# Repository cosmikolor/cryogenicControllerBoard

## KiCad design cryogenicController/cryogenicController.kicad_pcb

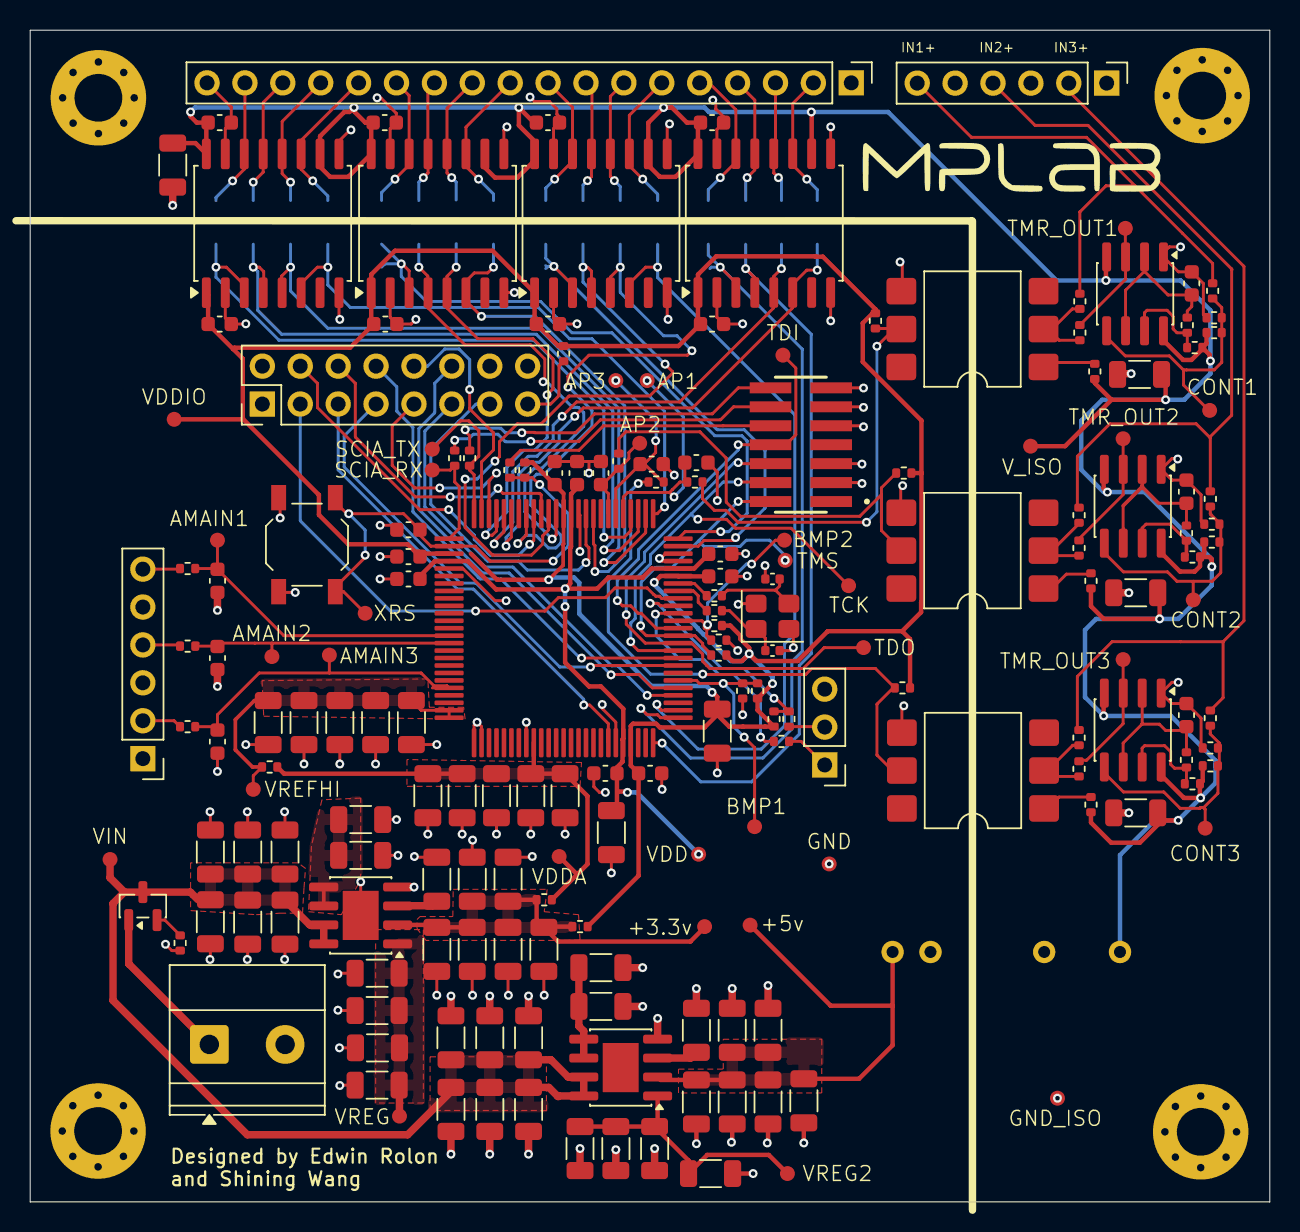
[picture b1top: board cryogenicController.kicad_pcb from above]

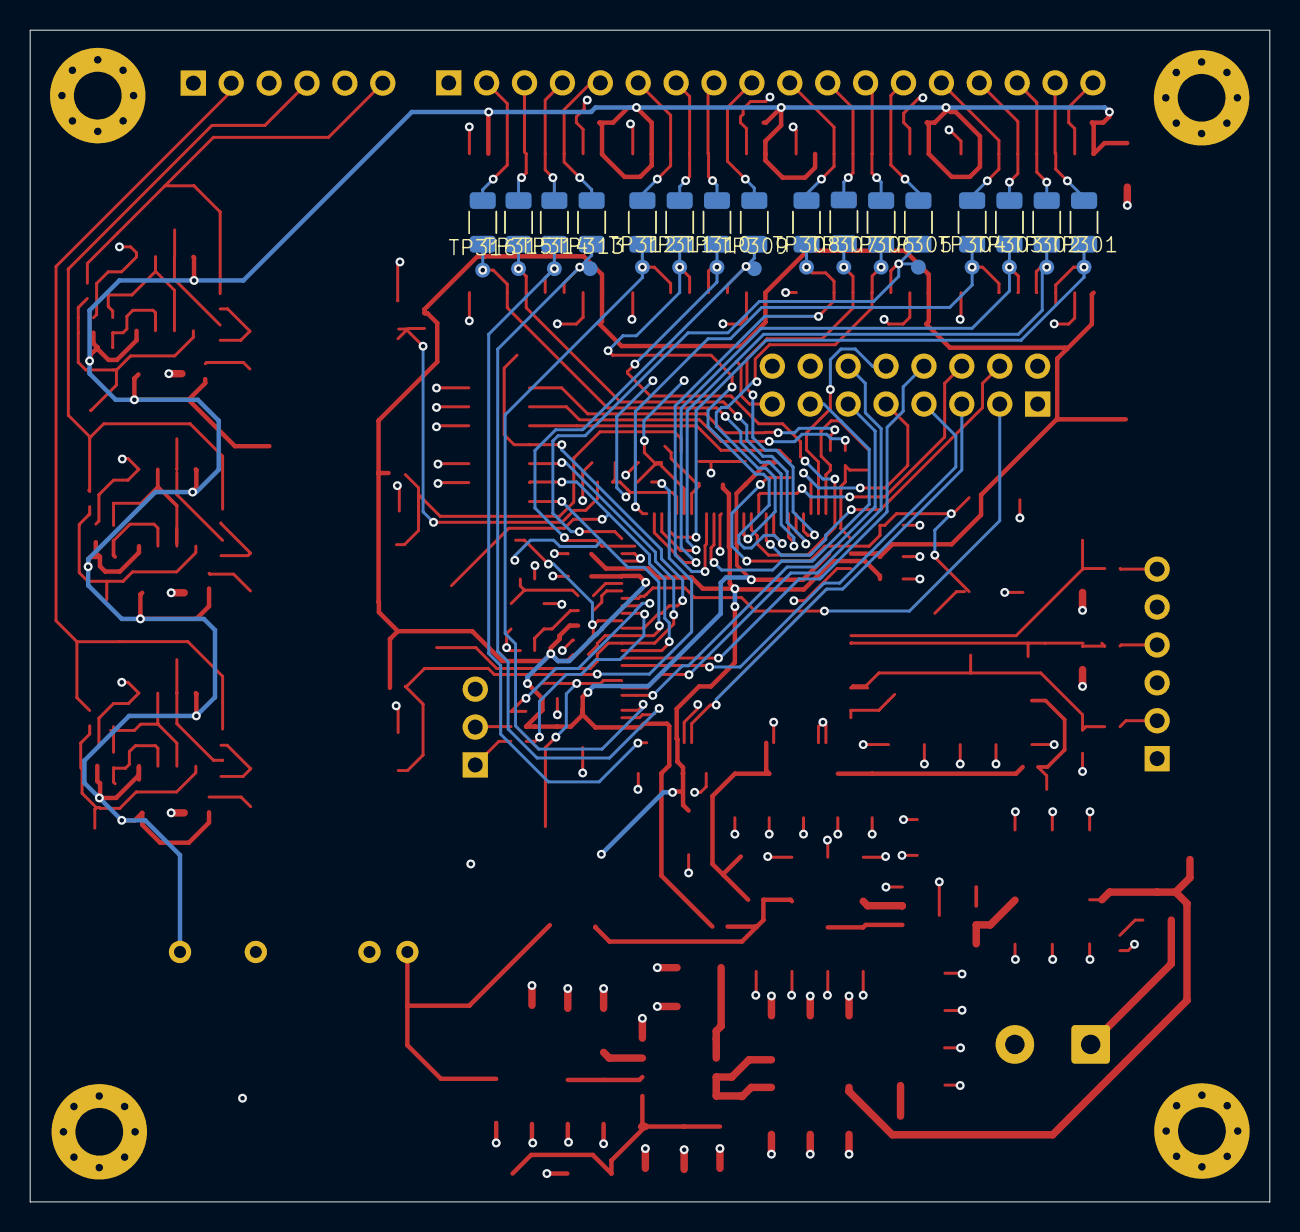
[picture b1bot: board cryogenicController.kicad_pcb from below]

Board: 4 copper layers, 83.1 x 78.5 mm, 223 parts (32 on the bottom side), 115 nets.

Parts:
+3.3v, +5v: TestPoint; Testpoint_1.0mm
AMAIN1, AMAIN2, AMAIN3: TestPoint; Testpoint_1.0mm
AP1, AP2, AP3: TestPoint; Testpoint_1.0mm
BMP1, BMP2: TestPoint; Testpoint_1.0mm
C201, C202, C203, C204, C205, C206, C207, C208, C209, C210, C211, C212, C213, C214, C215, C216, C217, C218, C219, C220, C221, C222, C223, C224, C225, C226, C227, C228, C229, C230, C231, C232, C233, C234, C235, C236, C237, C238, C301, C402, C405, C408, C503, C504, C505, C506, C507, C510, C511, C514, C515, C519, C522, C523: 470nF; C_1206_3216Metric
C302, C303, C304, C305, C306, C307, C308, C309, C401, C403, C404, C406, C407, C409, C410, C411, C412, C508, C509, C512, C513, C516, C517, C518, C520, C521: 18nF; C_0603_1608Metric
C501, C502: 12pF; C_0402_1005Metric
CONT1, CONT2, CONT3: TestPoint; Testpoint_1.0mm
GND: TestPoint; Testpoint_1.0mm
GND_ISO: TestPoint; Testpoint_1.0mm
J1, J2: Conn_01x06; PinHeader_1x06_P2.54mm_Vertical
J201: Screw_Terminal_01x02; TerminalBlock_Phoenix_MKDS-1,5-2-5.08_1x02_P5.08mm_Horizont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
J301: Conn_01x18_Pin; PinHeader_1x18_P2.54mm_Vertical
J501: Conn_02x08_Odd_Even; PinHeader_2x08_P2.54mm_Vertical
J601: Conn_02x07_Odd_Even; SAMTEC_FTSH-107-01-X-DV-K
J602: Conn_01x03_Pin; PinHeader_1x03_P2.54mm_Vertical
Q201: PMOS; SOT-23
R201: 10K; R_0402_1005Metric
R301, R302, R304, R305, R306, R307, R308, R309, R310, R311, R312, R313, R314, R315, R316, R317: 0; R_1206_3216Metric
R401, R411, R421: 2.49k; R_0402_1005Metric
R402, R407, R412, R419, R422, R429, R506, R507, R510, R607: 10k; R_0402_1005Metric
R403, R413, R423: 4.02k; R_0402_1005Metric
R404, R414, R424: 4.7k; R_0402_1005Metric
R405, R415, R425: 22k; R_0402_1005Metric
R406, R417, R427: 390; R_0402_1005Metric
R408, R409, R416, R418, R426, R428, R501, R502, R503, R504, R505, R511, R602, R603, R604, R605, R606: 0; R_0402_1005Metric
R410, R420, R430, R431, R432, R433: 100; R_0402_1005Metric
R508, R509: 1k; R_0402_1005Metric
R601: 2.2K; R_0402_1005Metric
SCIA_RX: TestPoint; Testpoint_1.0mm
SCIA_TX: TestPoint; Testpoint_1.0mm
SW501: RESET; SW_SPST_TL3342
TCK: TestPoint; Testpoint_1.0mm
TDI: TestPoint; Testpoint_1.0mm
TDO: TestPoint; Testpoint_1.0mm
TMR_OUT1, TMR_OUT2, TMR_OUT3: TestPoint; Testpoint_1.0mm
TMS: TestPoint; Testpoint_1.0mm
TP301, TP302, TP303, TP304, TP305, TP306, TP307, TP308, TP309, TP310, TP311, TP312, TP313, TP314, TP315, TP316: TestPoint; Testpoint_1.0mm
U1: F280039CSPZ; F280039CSPZR
U2: MDS01M-12N
U201: ADM7150ARDZ-3.3-R7; SOIC-8-1EP_3.9x4.9mm_P1.27mm_EP2.41x3.3mm
U202: ADM7150ARDZ-5.0-R7; SOIC-8-1EP_3.9x4.9mm_P1.27mm_EP2.41x3.3mm
U402, U404, U406: TLC555xD; SOIC-8_3.9x4.9mm_P1.27mm
U403, U405, U407: 4N25SM; SMDIP-6_W9.53mm
U_ISO301, U_ISO302, U_ISO303, U_ISO304: MAX14434FAWE+; SOIC-16W_7.5x10.3mm_P1.27mm
VDD: TestPoint; Testpoint_1.0mm
VDDA: TestPoint; Testpoint_1.0mm
VDDIO: TestPoint; Testpoint_1.0mm
VIN: TestPoint; Testpoint_1.0mm
VREFHI: TestPoint; Testpoint_1.0mm
VREG, VREG2: TestPoint; Testpoint_1.0mm
V_ISO: TestPoint; Testpoint_1.0mm
XRS: TestPoint; Testpoint_1.0mm
Y501: Crystal_GND24; Crystal_SMD_3225-4Pin_3.2x2.5mm

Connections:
+3.3V: +3.3v.1 (1_1), C214.2, C215.2, C216.2, C217.2, C218.2, C219.2, R504.1, R505.1, U201.2 (VOUT)
+5V: +5v.1 (1_1), C233.2, C234.2, C235.2, C236.2, C237.2, C238.2, U2.1 (+Vin), U202.2 (VOUT)
/ISOLATED_ANALOG_INPUT/ANALOG_PULSE1: AP1.1 (1_1), C404.2, R410.1, U1.80 (GPIO40)
/ISOLATED_ANALOG_INPUT/ANALOG_PULSE2: AP2.1 (1_1), C409.2, R430.1, U1.82 (GPIO41)
/ISOLATED_ANALOG_INPUT/ANALOG_PULSE3: AP3.1 (1_1), C406.2, R420.1, U1.81 (GPIO23)
/ISOLATED_ANALOG_INPUT/CONT1: CONT1.1 (1_1), R401.2, R402.1, R403.2, U402.5 (CONT)
/ISOLATED_ANALOG_INPUT/CONT2: CONT2.1 (1_1), R421.2, R422.1, R423.2, U406.5 (CONT)
/ISOLATED_ANALOG_INPUT/CONT3: CONT3.1 (1_1), R411.2, R412.1, R413.2, U404.5 (CONT)
/ISOLATED_ANALOG_INPUT/IN1+: J2.6, R401.1, R409.2
/ISOLATED_ANALOG_INPUT/IN2+: J2.4, R421.1, R428.2
/ISOLATED_ANALOG_INPUT/IN3+: J2.2, R411.1, R418.2
/ISOLATED_ANALOG_INPUT/TMR_OUT1: R408.2, TMR_OUT1.1 (1_1), U402.3 (OUT)
/ISOLATED_ANALOG_INPUT/TMR_OUT2: R426.2, TMR_OUT2.1 (1_1), U406.3 (OUT)
/ISOLATED_ANALOG_INPUT/TMR_OUT3: R416.2, TMR_OUT3.1 (1_1), U404.3 (OUT)
/ISOLATED_IO/PWM1_A: R301.2, TP301.1 (1_1), U1.79 (GPIO0), U_ISO301.3 (IN1)
/ISOLATED_IO/PWM1_A_ISO: J301.17, R301.1, U_ISO301.14 (OUT1)
/ISOLATED_IO/PWM1_B: R304.2, TP302.1 (1_1), U1.78 (GPIO1), U_ISO301.4 (IN2)
/ISOLATED_IO/PWM1_B_ISO: J301.16, R304.1, U_ISO301.13 (OUT2)
/ISOLATED_IO/PWM2_A: R306.2, TP303.1 (1_1), U1.77 (GPIO2), U_ISO301.5 (IN3)
/ISOLATED_IO/PWM2_A_ISO: J301.15, R306.1, U_ISO301.12 (OUT3)
/ISOLATED_IO/PWM2_B: R308.2, TP304.1 (1_1), U1.76 (GPIO3), U_ISO301.6 (IN4)
/ISOLATED_IO/PWM2_B_ISO: J301.14, R308.1, U_ISO301.11 (OUT4)
/ISOLATED_IO/PWM3_A: R302.2, TP305.1 (1_1), U1.75 (GPIO4), U_ISO302.3 (IN1)
/ISOLATED_IO/PWM3_A_ISO: J301.13, R302.1, U_ISO302.14 (OUT1)
/ISOLATED_IO/PWM3_B: R305.2, TP306.1 (1_1), U1.89 (GPIO5), U_ISO302.4 (IN2)
/ISOLATED_IO/PWM3_B_ISO: J301.12, R305.1, U_ISO302.13 (OUT2)
/ISOLATED_IO/PWM4_A: R307.2, TP307.1 (1_1), U1.97 (GPIO6), U_ISO302.5 (IN3)
/ISOLATED_IO/PWM4_A_ISO: J301.11, R307.1, U_ISO302.12 (OUT3)
/ISOLATED_IO/PWM4_B: R309.2, TP308.1 (1_1), U1.84 (GPIO7), U_ISO302.6 (IN4)
/ISOLATED_IO/PWM4_B_ISO: J301.10, R309.1, U_ISO302.11 (OUT4)
/ISOLATED_IO/PWM5_A: R310.2, TP309.1 (1_1), U1.74 (GPIO8), U_ISO303.3 (IN1)
/ISOLATED_IO/PWM5_A_ISO: J301.9, R310.1, U_ISO303.14 (OUT1)
/ISOLATED_IO/PWM5_B: R312.2, TP310.1 (1_1), U1.90 (GPIO9), U_ISO303.4 (IN2)
/ISOLATED_IO/PWM5_B_ISO: J301.8, R312.1, U_ISO303.13 (OUT2)
/ISOLATED_IO/PWM6_A: R314.2, TP311.1 (1_1), U1.93 (GPIO10), U_ISO303.5 (IN3)
/ISOLATED_IO/PWM6_A_ISO: J301.7, R314.1, U_ISO303.12 (OUT3)
/ISOLATED_IO/PWM6_B: R316.2, TP312.1 (1_1), U1.52 (GPIO11), U_ISO303.6 (IN4)
/ISOLATED_IO/PWM6_B_ISO: J301.6, R316.1, U_ISO303.11 (OUT4)
/ISOLATED_IO/PWM7_A: R311.2, TP313.1 (1_1), U1.51 (GPIO12), U_ISO304.3 (IN1)
/ISOLATED_IO/PWM7_A_ISO: J301.5, R311.1, U_ISO304.14 (OUT1)
/ISOLATED_IO/PWM7_B: R313.2, TP314.1 (1_1), U1.50 (GPIO13), U_ISO304.4 (IN2)
/ISOLATED_IO/PWM7_B_ISO: J301.4, R313.1, U_ISO304.13 (OUT2)
/ISOLATED_IO/PWM8_A: R315.2, TP315.1 (1_1), U1.96 (GPIO14), U_ISO304.5 (IN3)
/ISOLATED_IO/PWM8_A_ISO: J301.3, R315.1, U_ISO304.12 (OUT3)
/ISOLATED_IO/PWM8_B: R317.2, TP316.1 (1_1), U1.95 (GPIO15), U_ISO304.6 (IN4)
/ISOLATED_IO/PWM8_B_ISO: J301.2, R317.1, U_ISO304.11 (OUT4)
/JTAG_UART/SCIA_RX: R602.1, SCIA_RX.1 (1_1), U1.1 (GPIO28)
/JTAG_UART/SCIA_TX: R603.1, SCIA_TX.1 (1_1), U1.100 (GPIO29)
/JTAG_UART/SCIB_RX: R606.2, R607.2, U1.66 (GPIO57)
/JTAG_UART/SCIB_TX: R605.1, U1.65 (GPIO56)
/JTAG_UART/TCK: J601.4, TCK.1 (1_1), U1.60 (TCK)
/JTAG_UART/TDI: J601.8, TDI.1 (1_1), U1.63 (GPIO35_TDI)
/JTAG_UART/TDO: J601.6, TDO.1 (1_1), U1.61 (GPIO37_TDO)
/JTAG_UART/TMS: J601.2, R601.1, TMS.1 (1_1), U1.62 (TMS)
/MAIN_ANALOG/ANALOG_MAIN1: AMAIN1.1 (1_1), C410.2, R431.1, U1.14 (A6)
/MAIN_ANALOG/ANALOG_MAIN2: AMAIN2.1 (1_1), C411.2, R432.1, U1.15 (B2_C6)
/MAIN_ANALOG/ANALOG_MAIN3: AMAIN3.1 (1_1), C412.2, R433.1, U1.21 (B12_C2)
/MCU/BMP1: BMP1.1 (1_1), R507.1, R508.1, U1.56 (GPIO24)
/MCU/BMP2: BMP2.1 (1_1), R509.1, R510.1, U1.64 (GPIO32)
/MCU/CANA_RX: J501.9, U1.98 (GPIO30)
/MCU/CANA_TX: J501.10, U1.99 (GPIO31)
/MCU/GPIO18_X2: R501.2, U1.68 (GPIO18_X2)
/MCU/GPIO19_X1: R502.2, U1.69 (GPIO19_X1)
/MCU/GPIO_SPARE1: J501.12, U1.55 (GPIO17)
/MCU/GPIO_SPARE2: J501.13, U1.85 (GPIO44)
/MCU/I2CA_SCL: J501.8, U1.59 (GPIO27)
/MCU/I2CA_SDA: J501.7, U1.58 (GPIO26)
/MCU/SPIB_CLK: J501.3, U1.67 (GPIO58)
/MCU/SPIB_SIMO: J501.5, U1.44 (GPIO60)
/MCU/SPIB_SOMI: J501.6, U1.91 (GPIO61)
/MCU/SPIB_STE: J501.4, U1.92 (GPIO59)
/MCU/VREFHI: C503.1, C506.1, C510.1, C514.1, C519.1, R503.1, U1.24 (VREFHI), U1.25 (VREFHI), VREFHI.1 (1_1)
/MCU/XCLKOUT: J501.11, U1.54 (GPIO16)
/MCU/XRS: C518.2, R506.2, R604.1, SW501.2, U1.2 (~XRS), XRS.1 (1_1)
/POWER/BYP: C209.2, U201.3 (BYP)
/POWER/BYP2: C228.2, U202.3 (BYP)
/POWER/REF: C207.2, C208.2, U201.5 (REF_SENSE), U201.6 (REF)
/POWER/REF2: C226.2, C227.2, U202.5 (REF_SENSE), U202.6 (REF)
/POWER/VIN: C201.2, C202.2, C203.2, C204.2, C205.2, C206.2, C220.2, C221.2, C222.2, C223.2, C224.2, C225.2, Q201.3 (S), U201.7 (EN), U201.8 (VIN), U202.7 (EN), U202.8 (VIN), VIN.1 (1_1)
/POWER/VREG: C210.2, C211.2, C212.2, C213.2, U201.1 (VREG), VREG.1 (1_1)
/POWER/VREG2: C229.2, C230.2, C231.2, C232.2, U202.1 (VREG), VREG2.1 (1_1)
GND: C201.1, C202.1, C203.1, C204.1, C205.1, C206.1, C207.1, C208.1, C209.1, C210.1, C211.1, C212.1, C213.1, C214.1, C215.1, C216.1, C217.1, C218.1, C219.1, C220.1, C221.1, C222.1, C223.1, C224.1, C225.1, C226.1, C227.1, C228.1, C229.1, C230.1, C231.1, C232.1, C233.1, C234.1, C235.1, C236.1, C237.1, C238.1, C306.2, C307.2, C308.2, C309.2, C404.1, C406.1, C409.1, C410.1, C411.1, C412.1, C501.2, C502.2, C503.2, C504.1, C505.1, C506.2, C507.1, C508.1, C509.1, C510.2, C511.1, C512.1, C513.1, C514.2, C515.1, C516.1, C517.1, C518.1, C519.2, C520.1, C521.1, C522.1, C523.1, GND.1 (1_1), J1.1, J1.3, J1.5, J201.2, J501.1, J501.2, J501.14, J501.16, J601.3, J601.5, J601.9, J601.11, J601.13, J602.3, R201.1, R508.2, R509.2, SW501.1, U1.5 (VSS), U1.26 (VREFLO), U1.27 (VREFLO), U1.33 (VSSA), U1.45 (VSS), U1.72 (VSS), U1.73 (~VREGEN), U1.86 (VSS), U2.2 (-Vin), U201.4 (GND), U201.EPAD, U202.4 (GND), U403.4, U405.4, U407.4, U_ISO301.2 (GNDA), U_ISO301.8 (GNDA), U_ISO302.2 (GNDA), U_ISO302.8 (GNDA), U_ISO303.2 (GNDA), U_ISO303.8 (GNDA), U_ISO304.2 (GNDA), U_ISO304.8 (GNDA), Y501.2 (G), Y501.4 (G)
GND_ISO: C301.1, C302.2, C303.1, C304.1, C305.1, C401.1, C402.1, C403.1, C405.1, C407.1, C408.1, GND_ISO.1 (1_1), J2.1, J2.3, J2.5, J301.1, J301.18, R403.1, R413.1, R423.1, U2.5 (0V), U402.1 (GND), U404.1 (GND), U406.1 (GND), U_ISO301.9 (GNDB), U_ISO301.15 (GNDB), U_ISO302.9 (GNDB), U_ISO302.15 (GNDB), U_ISO303.9 (GNDB), U_ISO303.15 (GNDB), U_ISO304.9 (GNDB), U_ISO304.15 (GNDB)
unnamed: C501.1, R501.1, Y501.1
unnamed: C502.1, R502.1, Y501.3
unnamed: J1.2, R433.2
unnamed: J1.4, R432.2
unnamed: J1.6, R431.2
unnamed: J201.1, Q201.1 (D)
unnamed: J501.15, R511.1
unnamed: J601.10, R604.2
unnamed: J601.12, R602.2
unnamed: J601.14, R603.2
unnamed: J602.1, R605.2
unnamed: J602.2, R606.1
unnamed: Q201.2 (G), R201.2
unnamed: R406.2, U403.1
unnamed: R407.1, R410.2, U403.5
unnamed: R408.1, R409.1, U403.2
unnamed: R416.1, R418.1, U405.2
unnamed: R417.2, U405.1
unnamed: R419.1, R420.2, U405.5
unnamed: R426.1, R428.1, U407.2
unnamed: R427.2, U407.1
unnamed: R429.1, R430.2, U407.5
unnamed: R404.2, R405.1, U402.7 (DISCH)
unnamed: C401.2, R405.2, U402.2 (TRIG), U402.6 (THRES)
unnamed: R414.2, R415.1, U404.7 (DISCH)
unnamed: C403.2, R415.2, U404.2 (TRIG), U404.6 (THRES)
unnamed: R424.2, R425.1, U406.7 (DISCH)
unnamed: C407.2, R425.2, U406.2 (TRIG), U406.6 (THRES)
VDD: C504.2, C508.2, C512.2, C516.2, C520.2, U1.4 (VDD), U1.46 (VDD), U1.71 (VDD), U1.87 (VDD), VDD.1 (1_1)
VDDA: C507.2, C511.2, C515.2, C522.2, C523.2, R503.2, R505.2, U1.34 (VDDA), VDDA.1 (1_1)
VDDIO: C306.1, C307.1, C308.1, C309.1, C505.2, C509.2, C513.2, C517.2, C521.2, R407.2, R419.2, R429.2, R504.2, R506.1, R507.2, R510.2, R511.2, R601.2, R607.1, U1.3 (VDDIO), U1.47 (VDDIO), U1.70 (VDDIO), U1.88 (VDDIO), U_ISO301.1 (VDDA), U_ISO302.1 (VDDA), U_ISO303.1 (VDDA), U_ISO304.1 (VDDA), VDDIO.1 (1_1)
V_ISO: C301.2, C302.1, C303.2, C304.2, C305.2, C402.2, C405.2, C408.2, R402.2, R404.1, R406.1, R412.2, R414.1, R417.1, R422.2, R424.1, R427.1, U2.7 (+12V), U402.4 (~RST), U402.8 (VCC), U404.4 (~RST), U404.8 (VCC), U406.4 (~RST), U406.8 (VCC), U_ISO301.10 (ENB), U_ISO301.16 (VDDB), U_ISO302.10 (ENB), U_ISO302.16 (VDDB), U_ISO303.10 (ENB), U_ISO303.16 (VDDB), U_ISO304.10 (ENB), U_ISO304.16 (VDDB), V_ISO.1 (1_1)
